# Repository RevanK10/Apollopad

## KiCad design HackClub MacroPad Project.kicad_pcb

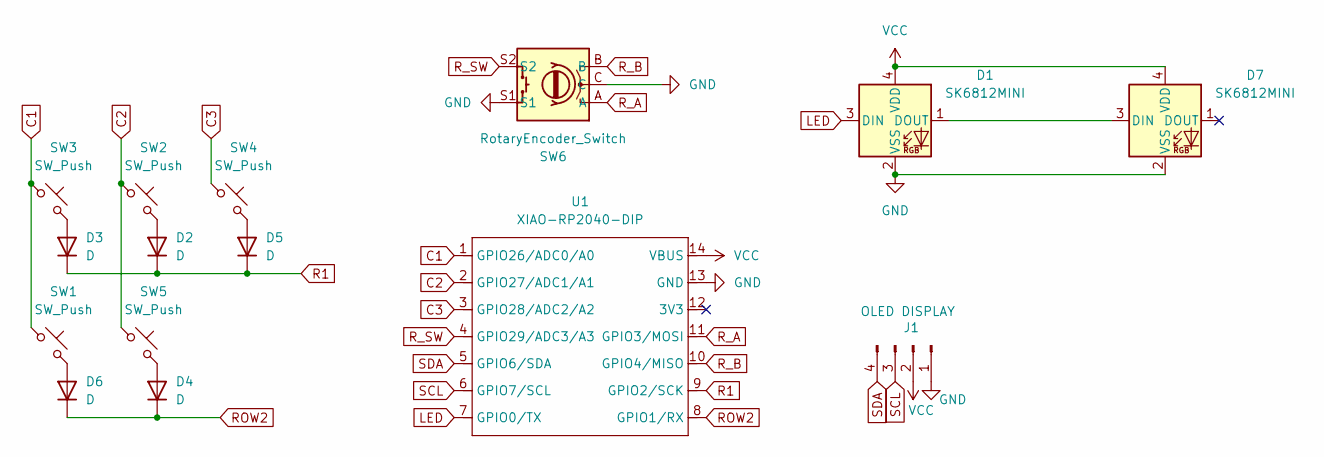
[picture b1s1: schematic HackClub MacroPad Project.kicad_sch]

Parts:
D1, D7: SK6812MINI; LED_SK6812MINI_PLCC4_3.5x3.5mm_P1.75mm
D2, D3, D4, D5, D6: D; D_DO-35_SOD27_P7.62mm_Horizontal
J1: OLED DISPLAY; SSD1306-0.91-OLED-4pin-128x32
SW1, SW2, SW3, SW4, SW5: SW_Push; SW_Cherry_MX_1.00u_PCB
SW6: RotaryEncoder_Switch; RotaryEncoder_Alps_EC11E-Switch_Vertical_H20mm
U1: XIAO-RP2040-DIP

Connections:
C1: SW1.1, SW3.1, U1.1 (GPIO26/ADC0/A0)
C2: SW2.1, SW5.1, U1.2 (GPIO27/ADC1/A1)
C3: SW4.1, U1.3 (GPIO28/ADC2/A2)
GND: D1.2 (VSS), D7.2 (VSS), J1.1, SW6.C, SW6.S1, U1.13 (GND)
LED: D1.3 (DIN), U1.7 (GPIO0/TX)
unnamed: D1.1 (DOUT), D7.3 (DIN)
unnamed: D2.2 (A), SW2.2
unnamed: D3.2 (A), SW3.2
unnamed: D4.2 (A), SW5.2
unnamed: D5.2 (A), SW4.2
unnamed: D6.2 (A), SW1.2
R1: D2.1 (K), D3.1 (K), D5.1 (K), U1.9 (GPIO2/SCK)
ROW2: D4.1 (K), D6.1 (K), U1.8 (GPIO1/RX)
R_A: SW6.A, U1.11 (GPIO3/MOSI)
R_B: SW6.B, U1.10 (GPIO4/MISO)
R_SW: SW6.S2, U1.4 (GPIO29/ADC3/A3)
SCL: J1.3, U1.6 (GPIO7/SCL)
SDA: J1.4, U1.5 (GPIO6/SDA)
VCC: D1.4 (VDD), D7.4 (VDD), J1.2, U1.14 (VBUS)

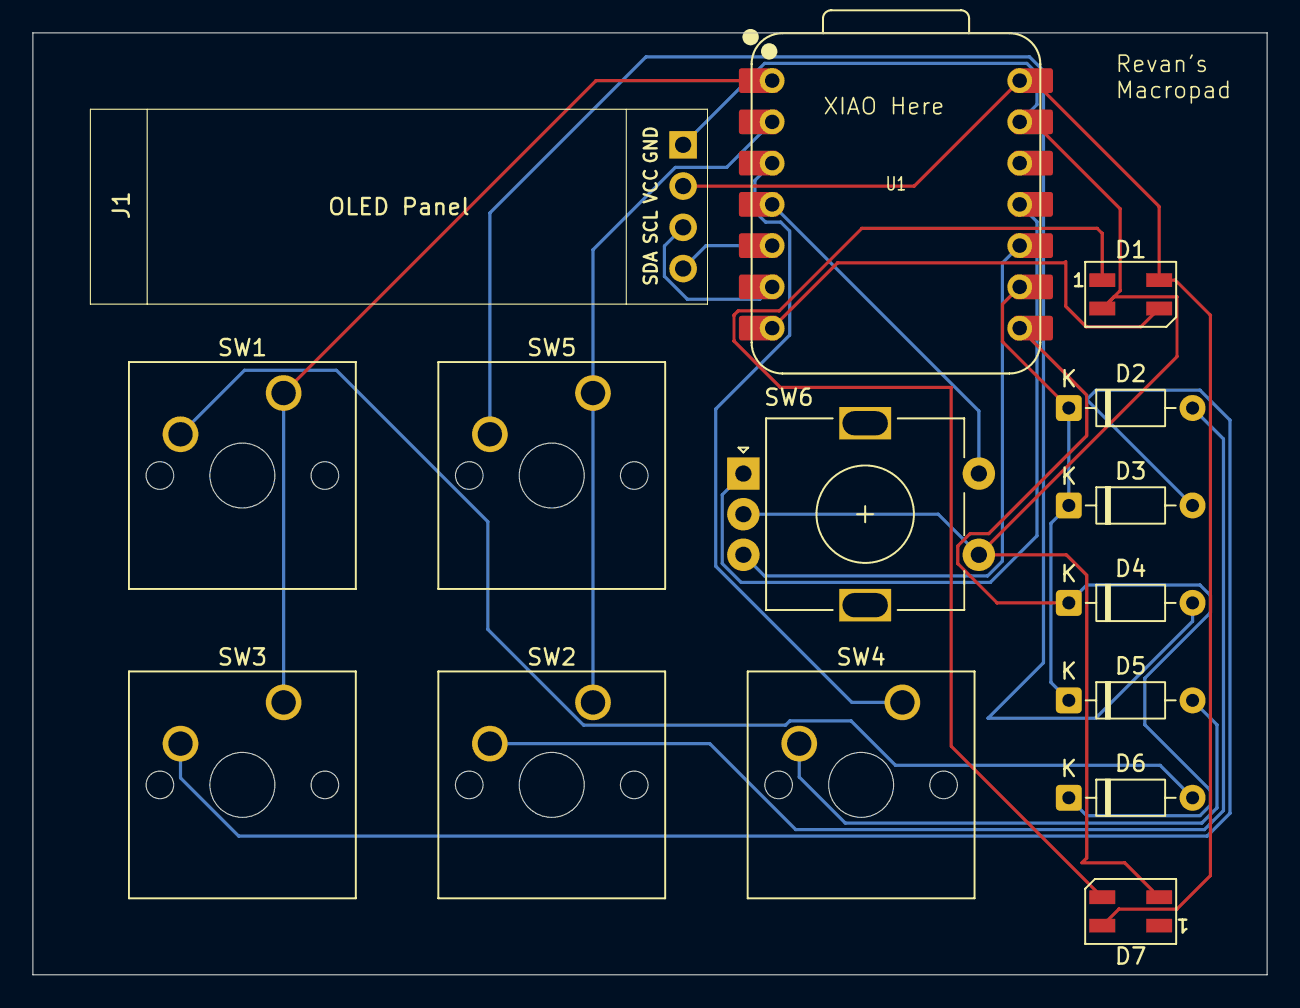
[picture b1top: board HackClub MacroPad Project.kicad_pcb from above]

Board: 2 copper layers, 76.0 x 58.0 mm, 15 parts (0 on the bottom side), 19 nets.

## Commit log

2026-06-02 Initial commit from local files
